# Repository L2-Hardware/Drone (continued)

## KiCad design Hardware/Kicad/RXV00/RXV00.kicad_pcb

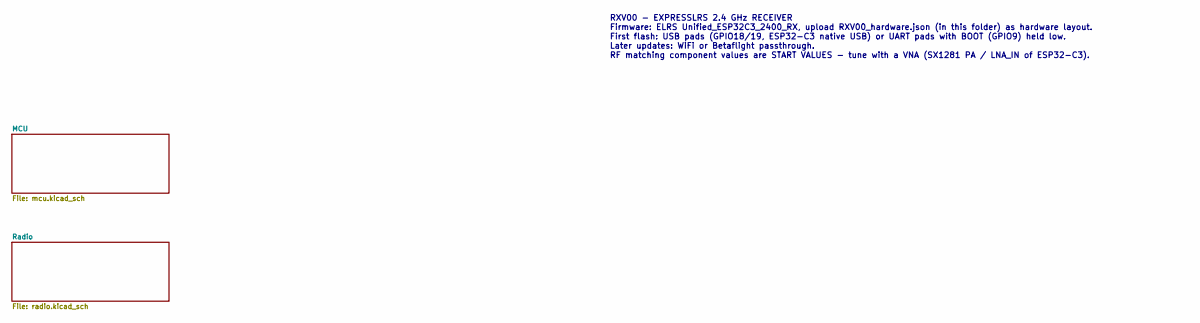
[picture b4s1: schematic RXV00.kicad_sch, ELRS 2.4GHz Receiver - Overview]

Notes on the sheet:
RXV00 - EXPRESSLRS 2.4 GHz RECEIVER Firmware: ELRS Unified_ESP32C3_2400_RX, upload RXV00_hardware.json (in this folder) as hardware layout. First flash: USB pads (GPIO18/19, ESP32-C3 native USB) or UART pads with BOOT (GPIO9) held low. Later updates: WiFi or Betaflight passthrough. RF matching comp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

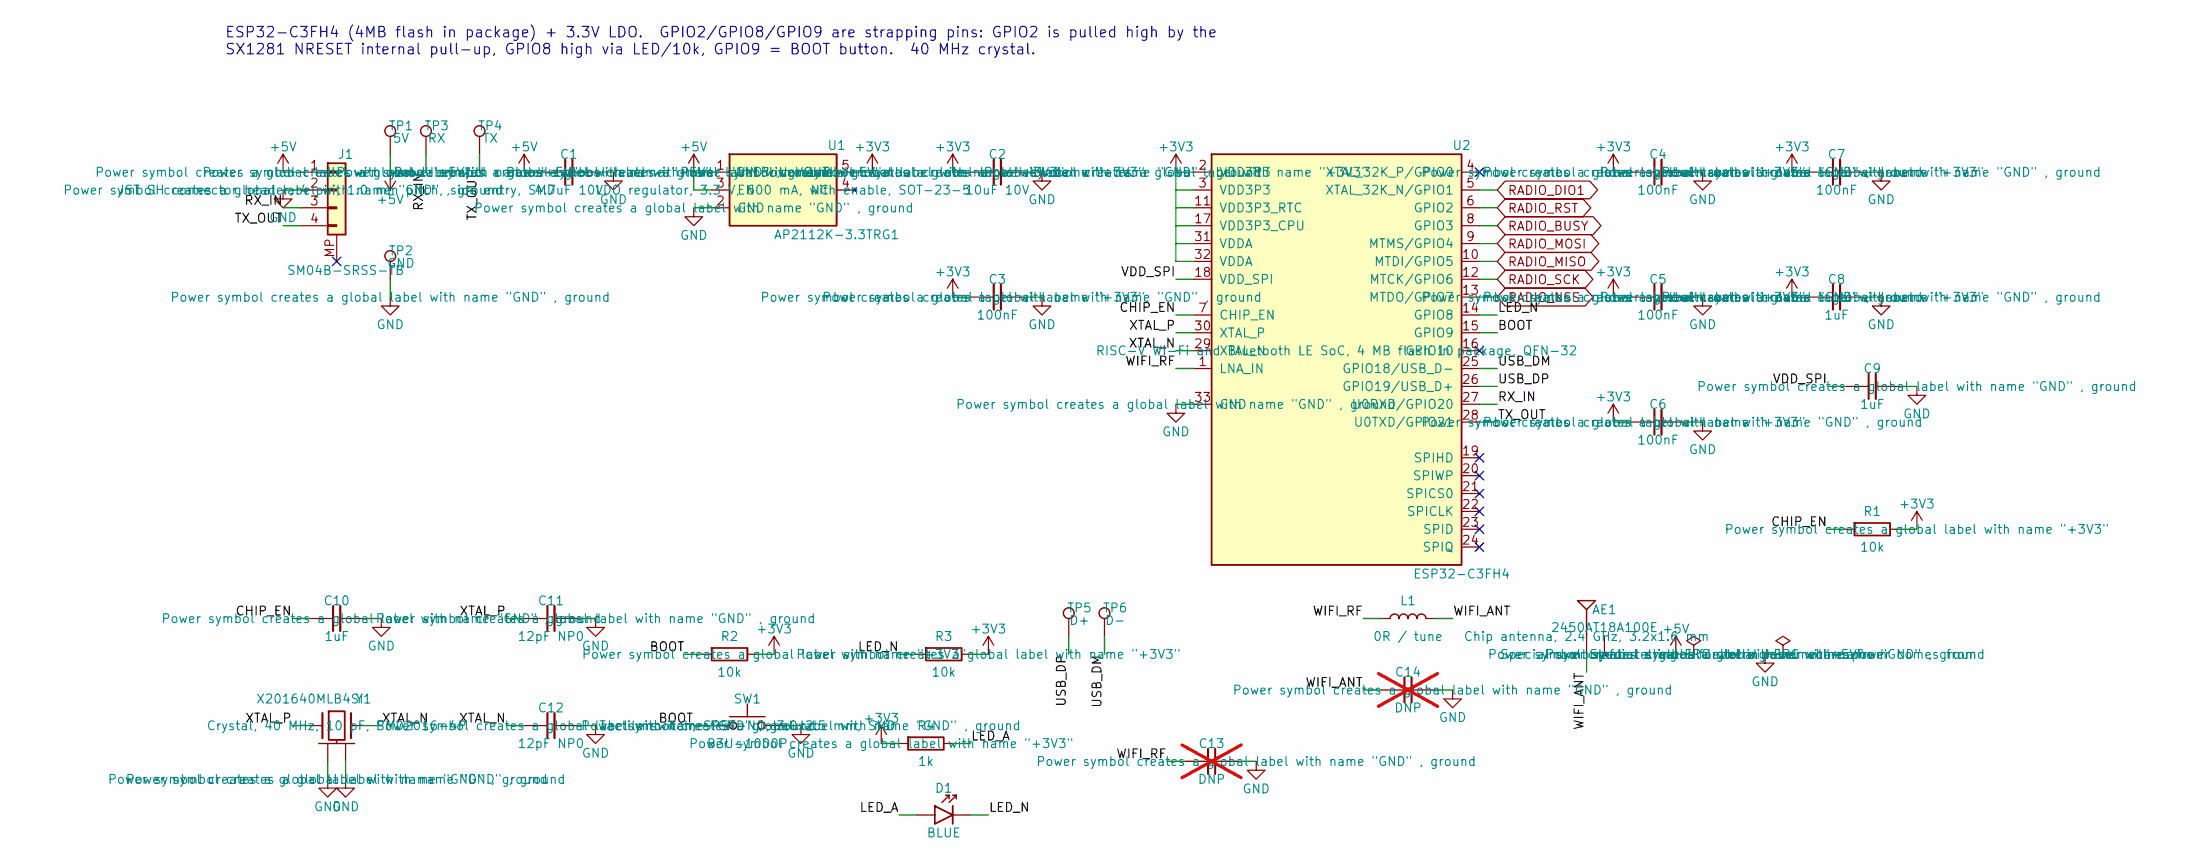
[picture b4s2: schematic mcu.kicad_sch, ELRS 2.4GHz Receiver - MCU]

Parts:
AE1: 2450AT18A100E
C1: 4.7uF 10V; C_0603_1608Metric
C2: 10uF 10V; C_0603_1608Metric
C3, C4, C5, C6, C7: 100nF; C_0402_1005Metric
C8, C9, C10: 1uF; C_0402_1005Metric
C11, C12: 12pF NP0; C_0402_1005Metric
C13, C14: DNP; C_0402_1005Metric; not fitted
D1: BLUE; LED_0603_1608Metric
J1: SM04B-SRSS-TB
L1: 0R / tune; L_0402_1005Metric
R1, R2, R3: 10k; R_0402_1005Metric
R4: 1k; R_0402_1005Metric
SW1: B3U-1000P
TP1: 5V; TestPoint_Pad_D1.5mm
TP2: GND; TestPoint_Pad_D1.5mm
TP3: RX; TestPoint_Pad_D1.5mm
TP4: TX; TestPoint_Pad_D1.5mm
TP5: D+; TestPoint_Pad_D1.0mm
TP6: D-; TestPoint_Pad_D1.0mm
U1: AP2112K-3.3TRG1
U2: ESP32-C3FH4
Y1: X201640MLB4SI

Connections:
+3V3: C2.1, C3.1, C4.1, C5.1, C6.1, C7.1, C8.1, R1.2, R2.2, R3.2, R4.1, U1.5 (VOUT), U2.2 (VDD3P3), U2.3 (VDD3P3), U2.11 (VDD3P3_RTC), U2.17 (VDD3P3_CPU), U2.31 (VDDA), U2.32 (VDDA); also elsewhere on the board
+5V: C1.1, J1.1, TP1.1, U1.1 (VIN), U1.3 (EN)
/MCU/BOOT: R2.1, SW1.1, U2.15 (GPIO9)
/MCU/CHIP_EN: C10.1, R1.1, U2.7 (CHIP_EN)
/MCU/LED_A: D1.2 (A), R4.2
/MCU/LED_N: D1.1 (K), R3.1, U2.14 (GPIO8)
/MCU/RX_IN: J1.3, TP3.1, U2.27 (U0RXD/GPIO20)
/MCU/TX_OUT: J1.4, TP4.1, U2.28 (U0TXD/GPIO21)
/MCU/USB_DM: TP6.1, U2.25 (GPIO18/USB_D-)
/MCU/USB_DP: TP5.1, U2.26 (GPIO19/USB_D+)
/MCU/VDD_SPI: C9.1, U2.18 (VDD_SPI)
/MCU/WIFI_ANT: AE1.1 (FEED), C14.1, L1.2
/MCU/WIFI_RF: C13.1, L1.1, U2.1 (LNA_IN)
/MCU/XTAL_N: C12.1, U2.29 (XTAL_N), Y1.3
/MCU/XTAL_P: C11.1, U2.30 (XTAL_P), Y1.1
GND: C1.2, C2.2, C3.2, C4.2, C5.2, C6.2, C7.2, C8.2, C9.2, C10.2, C11.2, C12.2, C13.2, C14.2, J1.2, SW1.2, TP2.1, U1.2 (GND), U2.33 (GND), Y1.2 (GND), Y1.4 (GND); also elsewhere on the board
RADIO_BUSY: U2.8 (GPIO3); also elsewhere on the board
RADIO_DIO1: U2.5 (XTAL_32K_N/GPIO1); also elsewhere on the board
RADIO_MISO: U2.10 (MTDI/GPIO5); also elsewhere on the board
RADIO_MOSI: U2.9 (MTMS/GPIO4); also elsewhere on the board
RADIO_NSS: U2.13 (MTDO/GPIO7); also elsewhere on the board
RADIO_RST: U2.6 (GPIO2); also elsewhere on the board
RADIO_SCK: U2.12 (MTCK/GPIO6); also elsewhere on the board

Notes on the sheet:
ESP32-C3FH4 (4MB flash in package) + 3.3V LDO. GPIO2/GPIO8/GPIO9 are strapping pins: GPIO2 is pulled high by the SX1281 NRESET internal pull-up, GPIO8 high via LED/10k, GPIO9 = BOOT button. 40 MHz crystal.

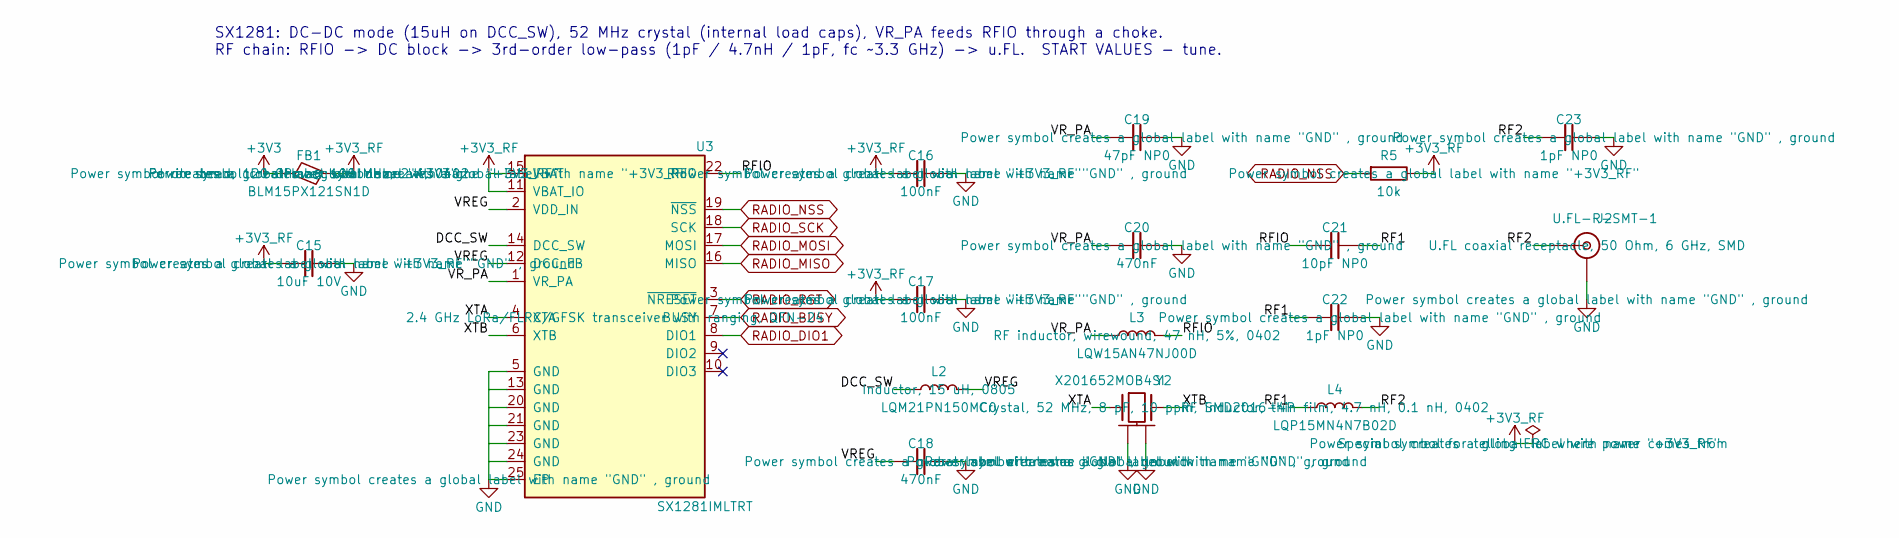
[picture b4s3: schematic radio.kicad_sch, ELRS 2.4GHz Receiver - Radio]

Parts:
C15: 10uF 10V; C_0603_1608Metric
C16, C17: 100nF; C_0402_1005Metric
C18, C20: 470nF; C_0402_1005Metric
C19: 47pF NP0; C_0402_1005Metric
C21: 10pF NP0; C_0402_1005Metric
C22, C23: 1pF NP0; C_0402_1005Metric
FB1: BLM15PX121SN1D
J2: U.FL-R-SMT-1
L2: LQM21PN150MC0
L3: LQW15AN47NJ00D
L4: LQP15MN4N7B02D
R5: 10k; R_0402_1005Metric
U3: SX1281IMLTRT
Y2: X201652MOB4SI

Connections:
+3V3: FB1.1; also elsewhere on the board
+3V3_RF: C15.1, C16.1, C17.1, FB1.2, R5.2, U3.11 (VBAT_IO), U3.15 (VBAT)
/Radio/DCC_SW: L2.1, U3.14 (DCC_SW)
/Radio/RF1: C21.2, C22.1, L4.1
/Radio/RF2: C23.1, J2.1 (In), L4.2
/Radio/RFIO: C21.1, L3.2, U3.22 (RFIO)
/Radio/VREG: C18.1, L2.2, U3.2 (VDD_IN), U3.12 (DCC_FB)
/Radio/VR_PA: C19.1, C20.1, L3.1, U3.1 (VR_PA)
/Radio/XTA: U3.4 (XTA), Y2.1
/Radio/XTB: U3.6 (XTB), Y2.3
GND: C15.2, C16.2, C17.2, C18.2, C19.2, C20.2, C22.2, C23.2, J2.2 (Ext), U3.5 (GND), U3.13 (GND), U3.20 (GND), U3.21 (GND), U3.23 (GND), U3.24 (GND), U3.25 (EP), Y2.2 (GND), Y2.4 (GND); also elsewhere on the board
RADIO_BUSY: U3.7 (BUSY); also elsewhere on the board
RADIO_DIO1: U3.8 (DIO1); also elsewhere on the board
RADIO_MISO: U3.16 (MISO); also elsewhere on the board
RADIO_MOSI: U3.17 (MOSI); also elsewhere on the board
RADIO_NSS: R5.1, U3.19 (~NSS); also elsewhere on the board
RADIO_RST: U3.3 (~NRESET); also elsewhere on the board
RADIO_SCK: U3.18 (SCK); also elsewhere on the board

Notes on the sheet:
SX1281: DC-DC mode (15uH on DCC_SW), 52 MHz crystal (internal load caps), VR_PA feeds RFIO through a choke. RF chain: RFIO -> DC block -> 3rd-order low-pass (1pF / 4.7nH / 1pF, fc ~3.3 GHz) -> u.FL. START VALUES - tune.

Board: 4 copper layers, 49 parts (0 on the bottom side), 32 nets, no tracks yet.

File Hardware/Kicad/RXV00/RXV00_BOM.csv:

"Qty","References","Value","Footprint","DNP"
"1","AE1","2450AT18A100E","eAntenna:2450AT18A100E",""
"1","C1","4.7uF 10V","eCapacitor:C_0603_1608Metric",""
"2","C2,C15","10uF 10V","eCapacitor:C_0603_1608Metric",""
"7","C3,C4,C5,C6,C7,C16,C17","100nF","eCapacitor:C_0402_1005Metric",""
"3","C8,C9,C10","1uF","eCapacitor:C_0402_1005Metric",""
"2","C11,C12","12pF NP0","eCapacitor:C_0402_1005Metric",""
"2","C13,C14","DNP","eCapacitor:C_0402_1005Metric","DNP"
"2","C18,C20","470nF","eCapacitor:C_0402_1005Metric",""
"1","C19","47pF NP0","eCapacitor:C_0402_1005Metric",""
"1","C21","10pF NP0","eCapacitor:C_0402_1005Metric",""
"2","C22,C23","1pF NP0","eCapacitor:C_0402_1005Metric",""
"1","D1","BLUE","eLED:LED_0603_1608Metric",""
"1","FB1","BLM15PX121SN1D","eFerrite:BLM15PX121SN1D",""
"1","J1","SM04B-SRSS-TB","eConnector:SM04B-SRSS-TB",""
"1","J2","U.FL-R-SMT-1","eConnector:U.FL-R-SMT-1",""
"1","L1","0R / tune","eCoil:L_0402_1005Metric",""
"1","L2","LQM21PN150MC0","eCoil:LQM21PN150MC0",""
"1","L3","LQW15AN47NJ00D","eCoil:LQW15AN47NJ00D",""
"1","L4","LQP15MN4N7B02D","eCoil:LQP15MN4N7B02D",""
"4","R1,R2,R3,R5","10k","eResistor:R_0402_1005Metric",""
"1","R4","1k","eResistor:R_0402_1005Metric",""
"1","SW1","B3U-1000P","eSwitch:B3U-1000P",""
"1","U1","AP2112K-3.3TRG1","eLinearReg:AP2112K-3.3TRG1",""
"1","U2","ESP32-C3FH4","eMCU:ESP32-C3FH4",""
"1","U3","SX1281IMLTRT","eRFModule:SX1281IMLTRT",""
"1","Y1","X201640MLB4SI","eCrystal:X201640MLB4SI",""
"1","Y2","X201652MOB4SI","eCrystal:X201652MOB4SI",""

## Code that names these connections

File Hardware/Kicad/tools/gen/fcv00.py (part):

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B.root_notes.append(
    "FCV00 - FLIGHT CONTROLLER\n"
    "MCU pin map (STM32F405RGT6)\n"
    "  SPI1 PA5/PA6/PA7  CS PA4  INT PC4  CLKIN PB0 -> ICM-42688-P (gyro)\n"
    "  SPI2 PB13/PB14/PB15  CS PB12        -> AT7456E (OSD)\n"
    "  SPI3 PB3/PB4/PB5  CS PA15           -> W25Q128 (blackbox)\n"
    "  I2C1 PB8/PB9                        -> LPS22DF baro + GPS compass\n"
    "  USART1 PB6/PB7 -> ELRS RX     USART2 PA2/PA3 -> VTX (MSP/SmartAudio)\n"
    "  USART3 PB10/PB11 -> GPS       UART4 PA0/PA1 -> AUX\n"
    "  UART5 PC12 (AUX TX) / PD2 (ESC telemetry RX)\n"
    "  MOTOR1..4 PC6..PC9 = TIM8 CH1..CH4 (DShot / bidir DShot)\n"
    "  LED strip PA8 (TIM1 CH1)   Buzzer PC5   LEDs PC14/PC15\n"
    "  ADC: VBAT PC2 (x11 divider), CURRENT PC1, USB VBUS detect PA9\n")

# ============================================================================ POWER
s = B.sheet("Power", "power.kicad_sch")
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for v, rtop, rbot, L, cout, rc, cc, chf in (("5V", "53.6k 1%", "10.2k 1%", "6.8uH SRP5030T-6R8M", "22uF 16V X5R", "16.9k", "6.8nF", "47pF"),
                                            ("10V", "115k 1%", "10k 1%", "10uH SRP5030T-100M", "22uF 25V X5R", "24.9k", "4.7nF", "33pF")):
    net = "+" + v
    s.add("eConverterDCDC:TPS54360BDDAR", pins={"VIN": "VBAT", "EN": "BUCK_EN", "RT/CLK": f"RT_{v}", "COMP": f"COMP_{v}",
                                                "GND": "GND", "GNDPAD": "GND", "BOOT": f"BOOT_{v}", "SW": f"SW_{v}", "FB": f"FB_{v}"})
    s.C("2.2uF 50V", "VBAT", fp=P.C0805)
    s.C("100nF 50V", "VBAT", fp=P.C0603)
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s = B.sheet("MCU", "mcu.kicad_sch")
s.note("MCU: STM32F405RGT6 168 MHz, HSE 8 MHz.  BOOT0 button = DFU over USB-C.  SWD on test pads.")
mcu = {
    "VBAT": "+3V3", "VDD": "+3V3", "VDDA": "VDDA", "NRST": "NRST", "BOOT0": "BOOT0", "PH0": "OSC_IN", "PH1": "OSC_OUT",
    "VCAP_1": "VCAP1", "VCAP_2": "VCAP2", "VSSA": "GND", "VSS": "GND",
    "PA0": "UART4_TX", "PA1": "UART4_RX", "PA2": "UART2_TX", "PA3": "UART2_RX", "PA4": "GYRO_CS", "PA5": "SPI1_SCK",
    "PA6": "SPI1_MISO", "PA7": "SPI1_MOSI", "PA8": "LED_STRIP", "PA9": "USB_VBUS_DET", "PA10": "NC", "PA11": "USB_DM",
    "PA12": "USB_DP", "PA13": "SWDIO", "PA14": "SWCLK", "PA15": "FLASH_CS",
    "PB0": "GYRO_CLKIN", "PB1": "PWM5", "PB2": "BOOT1", "PB3": "SPI3_SCK", "PB4": "SPI3_MISO", "PB5": "SPI3_MOSI",
    "PB6": "UART1_TX", "PB7": "UART1_RX", "PB8": "I2C1_SCL", "PB9": "I2C1_SDA", "PB10": "UART3_TX", "PB11": "UART3_RX",
    "PB12": "OSD_CS", "PB13": "SPI2_SCK", "PB14": "SPI2_MISO", "PB15": "SPI2_MOSI",
    "PC0": "NC", "PC1": "CURR_ADC", "PC2": "VBAT_ADC", "PC3": "NC", "PC4": "GYRO_INT1", "PC5": "BUZZER",
    "PC6": "MOTOR1", "PC7": "MOTOR2", "PC8": "MOTOR3", "PC9": "MOTOR4", "PC10": "NC", "PC11": "NC", "PC12": "UART5_TX",
    "PC13": "NC", "PC14": "LED0", "PC15": "LED1", "PD2": "UART5_RX"}
s.add("eMCU:STM32F405RGT6", pins=mcu)
for _ in range(5):
    s.C("100nF", "+3V3")
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    s.R("1k", "+3V3", f"{led}_A")
    s.LED(col, f"{led}_A", led)
# USB-C
s.add("eConnector:USB_C_GCT_USB4105-GF-A", pins={"VBUS": "VBUS", "CC1": "USB_CC1", "CC2": "USB_CC2", "D+": "USB_DP",
                                                  "D-": "USB_DM", "SBU1": "NC", "SBU2": "NC", "GND": "GND", "SHIELD": "GND"})
s.R("5.1k", "USB_CC1", "GND")
s.R("5.1k", "USB_CC2", "GND")
s.add("eDiodes:USBLC6-2SC6", pins={"I/O1": "USB_DP", "I/O2": "USB_DM", "VBUS": "VBUS", "GND": "GND"})
s.C("1uF 16V", "VBUS")
s.R("10k", "VBUS", "USB_VBUS_DET")
s.R("20k", "USB_VBUS_DET", "GND")

# ============================================================================ SENSORS
s = B.sheet("Sensors", "sensors.kicad_sch")
s.note("SENSORS: ICM-42688-P on dedicated SPI1 + own LDO (+3V3_GYRO). INT2/CLKIN driven by PB0 (TIM3) for external 32 kHz clock.\n"
       "LPS22DF baro on I2C1 (addr 0x5C, SA0=0). W25Q128JV blackbox flash on SPI3.")
s.add("eSensor:ICM-42688-P", pins={"VDD": "+3V3_GYRO", "VDDIO": "+3V3_GYRO", "AP_CS": "GYRO_CS", "AP_SCL/AP_SCLK": "SPI1_SCK",
                                    "AP_SDA/AP_SDIO/AP_SDI": "SPI1_MOSI", "AP_SDO/AP_AD0": "SPI1_MISO", "GND": "GND",
                                    "INT1/INT": "GYRO_INT1", "INT2/FSYNC/CLKIN": "GYRO_CLKIN"})
s.C("100nF", "+3V3_GYRO")
s.C("1uF", "+3V3_GYRO")
s.C("100nF", "+3V3_GYRO")
s.R("10k", "GYRO_CS", "+3V3_GYRO")
s.add("eSensor:LPS22DF", pins={"VDD": "+3V3", "Vdd_IO": "+3V3", "SCL": "I2C1_SCL", "SDA": "I2C1_SDA", "SA0": "GND",
                                "~{CS}": "+3V3", "INT_DRDY": "NC", "GND_IO": "GND", "GND": "GND"})
s.C("100nF", "+3V3")
s.R("2.2k", "I2C1_SCL", "+3V3")
s.R("2.2k", "I2C1_SDA", "+3V3")
s.add("eMemory:W25Q128JVSIQ", pins={"VCC": "+3V3", "~{CS}": "FLASH_CS", "CLK": "SPI3_SCK", "DI(IO0)": "SPI3_MOSI",
                                     "DO(IO1)": "SPI3_MISO", "IO2": "FLASH_WP", "IO3": "FLASH_HOLD", "GND": "GND"})
s.C("100nF", "+3V3")
s.R("10k", "FLASH_CS", "+3V3")
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       "J ESC 8p: VBAT GND CURR TLM M1 M2 M3 M4 (matches ESCV00)   J RX 4p: 5V GND TX RX (matches RXV00)\n"
       "J VTX 6p: 10V 5V GND VIDEO TX RX (matches VTXV00)   J CAM 3p: PWR GND VIDEO (PWR = 5V or 10V by solder jumper)\n"
       "J GPS 6p: 5V GND TX RX SCL SDA     J AUX 6p: 5V GND UART4_TX UART4_RX UART5_TX PWM5")
s.add("eConnector:JST_SH_SM08B-SRSS-TB", "ESC", pins={"1": "VBAT", "2": "GND", "3": "ESC_CURR", "4": "UART5_RX", "5": "MOTOR1",
                                                       "6": "MOTOR2", "7": "MOTOR3", "8": "MOTOR4", "MP": "NC"})
s.R("1k", "ESC_CURR", "CURR_ADC")
s.C("100nF", "CURR_ADC")
s.add("eConnector:JST_SH_SM04B-SRSS-TB", "RX", pins={"1": "+5V", "2": "GND", "3": "UART1_TX", "4": "UART1_RX", "MP": "NC"})
s.add("eConnector:JST_SH_SM06B-SRSS-TB", "VTX", pins={"1": "+10V", "2": "+5V", "3": "GND", "4": "VID_OUT", "5": "UART2_TX",
                                                       "6": "UART2_RX", "MP": "NC"})
s.add("eConnector:JST_SH_SM03B-SRSS-TB", "CAM", pins={"1": "CAM_PWR", "2": "GND", "3": "CAM_VIDEO", "MP": "NC"})
s.add("eJumpers:SolderJumper_3", "CAM 5V|10V", pins={"1": "+5V", "2": "CAM_PWR", "3": "+10V"})
s.C("10uF 25V", "CAM_PWR", fp=P.C0805)
s.add("eConnector:JST_SH_SM06B-SRSS-TB", "GPS", pins={"1": "+5V", "2": "GND", "3": "UART3_TX", "4": "UART3_RX", "5": "I2C1_SCL",
                                                       "6": "I2C1_SDA", "MP": "NC"})
s.add("eConnector:JST_SH_SM06B-SRSS-TB", "AUX", pins={"1": "+5V", "2": "GND", "3": "UART4_TX", "4": "UART4_RX", "5": "UART5_TX",
                                                       "6": "PWM5", "MP": "NC"})
# LED strip + buzzer pads
s.R("33R", "LED_STRIP", "LED_DOUT")
s.TP("LED_DOUT", P.TP20, "LED")
s.TP("+5V", P.TP20, "5V")
s.TP("GND", P.TP20, "GND")
s.add("eTransistor:2N7002", pins={"G": "BUZZER_G", "S": "GND", "D": "BUZZER_N"})
s.R("1k", "BUZZER", "BUZZER_G")
s.R("100k", "BUZZER_G", "GND")
s.D("D", "1N4148W", "BUZZER_N", "+5V", P.D_SOD123, fields={"MPN": "1N4148W"})
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
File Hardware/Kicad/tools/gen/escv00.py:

"""ESCV00 - 4-in-1 ESC for AM32 firmware.

Per channel: STM32F051K8U6 (or pin-compatible AT32F421K8U7) + DRV8300D 3-phase gate driver + 6x BSZ018N04LS6.
Pin-out follows AM32 HARDWARE_GROUP_F0_B / HARDWARE_GROUP_AT_B + AT_045 (same pins on both MCUs):
  input PB4 (TIM3_CH1), phase A: PA10 high / PB1 low, B: PA9 / PB0, C: PA8 / PA7,
  comparator: PA0 = phase A, PA4 = phase B, PA5 = phase C, PA1 = virtual neutral (COMP1 INP),
  VBAT ADC PA6 (10k/1k divider, AM32 default VOLTAGE_DIVIDER 110), telemetry TX PB6 (USART1).
"""
import parts as P
import project
from schgen import Board

B = Board("ESCV00", "4-in-1 ESC", "V00",
          comments=["4x (STM32F051K8U6 / AT32F421K8U7 + DRV8300D + 6x BSZ018N04LS6), AM32 firmware",
                    "2S-6S, 30.5x30.5 mm pattern, 6-layer 2oz recommended",
                    "Total current shunt 0.25 mOhm + INA181A3 -> 25 mV/A to FC"])
B.root_notes.append(
    "ESCV00 - 4-IN-1 ESC (AM32)\n"
    "Channel sheet is used 4 times (CH1..CH4 -> MOTOR1..4, M1_x..M4_x).\n"
    "Flash the AM32 bootloader once per MCU via the SWD pads (SWDIO/SWCLK/NRST + 3V3/GND),\n"
    "then update firmware over the signal wire (Betaflight passthrough / AM32 configurator).\n"
    "AM32 target: F051 -> HARDWARE_GROUP_F0_B, AT32F421 -> HARDWARE_GROUP_AT_B + HARDWARE_GROUP_AT_045\n"
    "  (identical to the TBS_6S_4IN1_F421 pin-out). Set DEAD_TIME to suit the DRV8300 + BSZ018N04LS6.\n"
    "Current: 4x 1 mOhm 2512 in parallel (0.25 mOhm) x INA181A3 (100 V/V) = 25 mV/A  -> Betaflight ibata_scale 250\n"
    "Battery voltage to FC: VBAT on connector pin 1 (FC measures it itself).\n")

# ============================================================================ CHANNEL (x4)
ch = B.sheet("Channel", "channel.kicad_sch",
             instances=[{"name": f"CH{i}", "ref_base": i * 100,
                         "portmap": {"SIG_IN": f"MOTOR{i}", "TLM": "ESC_TLM", "PH_A": f"M{i}_A", "PH_B": f"M{i}_B",
                                     "PH_C": f"M{i}_C"}} for i in (1, 2, 3, 4)],
             ports=["SIG_IN", "TLM", "PH_A", "PH_B", "PH_C"], globals_=["ESC_VBAT_SENSE"])
ch.note("ESC CHANNEL: MCU (AM32) -> DRV8300D (bootstrap diodes integrated, MODE/DT open = non-inverted, fixed dead time)\n"
        "Back-EMF sense: phase dividers 20k/2.2k to PA0/PA4/PA5, virtual neutral 3x 20k + 750R to PA1.  Gate R 4.7R.")
ch.add("eMCU:STM32F051K8U6", pins={
    "VDD": "+3V3", "VDDA": "VDDA", "NRST": "NRST", "BOOT0": "BOOT0", "PF0": "NC", "PF1": "NC", "VSS": "GND",
    "PA0": "SENSE_A", "PA1": "SENSE_N", "PA2": "NC", "PA3": "NC", "PA4": "SENSE_B", "PA5": "SENSE_C",
    "PA6": "ESC_VBAT_SENSE", "PA7": "C_LO", "PA8": "C_HI", "PA9": "B_HI", "PA10": "A_HI", "PA11": "NC", "PA12": "NC",
    "PA13": "SWDIO", "PA14": "SWCLK", "PA15": "NC", "PB0": "B_LO", "PB1": "A_LO", "PB2": "NC", "PB3": "NC",
    "PB4": "SIG_MCU", "PB5": "NC", "PB6": "TLM_MCU", "PB7": "NC", "PB8": "NC"})
ch.C("100nF", "+3V3")
ch.C("100nF", "+3V3")
ch.C("1uF", "+3V3")
ch.FB("120R@100MHz", "+3V3", "VDDA", fp=P.FB0402, fields={"MPN": "BLM15PX121SN1D"})
ch.C("1uF", "VDDA")
ch.C("100nF", "VDDA")
ch.R("10k", "BOOT0", "GND")
ch.C("100nF", "NRST")
ch.R("100R", "SIG_IN", "SIG_MCU")
ch.R("1k", "TLM_MCU", "TLM")
for n in ("SWDIO", "SWCLK", "NRST"):
    ch.TP(n, P.TP10)
ch.add("eInterface:DRV8300DRGER", pins={
    "GVDD": "+10V", "GND": "GND", "EP": "GND", "MODE": "NC", "DT": "NC",
    "INHA": "A_HI", "INLA": "A_LO", "INHB": "B_HI", "INLB": "B_LO", "INHC": "C_HI", "INLC": "C_LO",
    "BSTA": "BST_A", "GHA": "GHA_DRV", "SHA": "PH_A", "GLA": "GLA_DRV",
    "BSTB": "BST_B", "GHB": "GHB_DRV", "SHB": "PH_B", "GLB": "GLB_DRV",
    "BSTC": "BST_C", "GHC": "GHC_DRV", "SHC": "PH_C", "GLC": "GLC_DRV"})
ch.C("10uF 25V", "+10V", fp=P.C0805)
ch.C("100nF", "+10V")
for ph in "ABC":
    ch.C("1uF 25V X7R", f"BST_{ph}", f"PH_{ph}", fp=P.C0603)
    ch.R("4.7R", f"GH{ph}_DRV", f"GH_{ph}")
    ch.R("4.7R", f"GL{ph}_DRV", f"GL_{ph}")
    ch.add("eTransistor:BSZ018N04LS6", pins={"G": f"GH_{ph}", "D": "VBAT", "S": f"PH_{ph}"})
    ch.add("eTransistor:BSZ018N04LS6", pins={"G": f"GL_{ph}", "D": f"PH_{ph}", "S": "GND"})
    ch.R("20k", f"PH_{ph}", f"SENSE_{ph}")
    ch.R("2.2k", f"SENSE_{ph}", "GND")
    ch.R("20k", f"PH_{ph}", "SENSE_N")
ch.R("750R", "SENSE_N", "GND")
ch.C("10uF 50V X7R", "VBAT", fp=P.C1206)
ch.C("10uF 50V X7R", "VBAT", fp=P.C1206)
ch.C("100nF 50V", "VBAT", fp=P.C0603)

# ============================================================================ POWER / IO
s = B.sheet("Power", "power.kicad_sch")
s.note("POWER: battery pads, current shunt (low side), 10V gate-driver rail (LMR16006Y, 2.1 MHz), 3.3V LDO for the 4 MCUs.\n"
       "Add a 470-1000uF 35V low-ESR electrolytic on the battery leads (not on the PCB).\n"
       "LMR16006: Vout = 0.765V x (1 + 121k/10k) = 10.0V.  Shunt: BAT- pad -> 4x 1mOhm -> board GND.")
s.TP("VBAT", P.PAD5x8, "BAT+")
s.TP("BAT_N", P.PAD5x8, "BAT-")
for _ in range(4):
    s.R("1mR 3W", "GND", "BAT_N", fp=P.R2512, fields={"MPN": "WSLP2512R0010FEA", "Manufacturer": "Vishay"})
s.R("10R", "GND", "ISNS_P")
s.R("10R", "BAT_N", "ISNS_N")
s.C("100nF", "ISNS_P", "ISNS_N")
s.add("eAmplifier:INA181A3IDBVR", pins={"V+": "+3V3", "GND": "GND", "+": "ISNS_P", "-": "ISNS_N", "REF": "GND", "~": "CURR_OUT"})
s.C("100nF", "+3V3")
s.R("1k", "CURR_OUT", "ESC_CURR")
s.C("10nF", "ESC_CURR")
# shared battery sense for the 4 MCUs (AM32 low-voltage cut-off / telemetry)
s.R("10k 1%", "VBAT", "ESC_VBAT_SENSE")
s.R("1k 1%", "ESC_VBAT_SENSE", "GND")
s.C("100nF", "ESC_VBAT_SENSE")
# 10 V gate driver rail
s.add("eConverterDCDC:LMR16006YDDCR", pins={"VIN": "VBAT", "~{SHDN}": "EN_10V", "GND": "GND", "CB": "CB_10V",
                                             "SW": "SW_10V", "FB": "FB_10V"})
s.R("100k", "VBAT", "EN_10V")
s.C("2.2uF 50V", "VBAT", fp=P.C0805)
s.C("100nF 50V", "VBAT", fp=P.C0603)
s.C("100nF", "CB_10V", "SW_10V")
s.D("D_Schottky", "PMEG6010CEH", "GND", "SW_10V", P.D_SOD123F, fields={"MPN": "PMEG6010CEH,115"})
s.L("10uH SWPA3012S-100MT", "SW_10V", "+10V", fp=P.L_SWPA3012, fields={"MPN": "SWPA3012S100MT", "Manufacturer": "Sunlord"})
s.R("121k 1%", "+10V", "FB_10V")
s.R("10k 1%", "FB_10V", "GND")
s.C("10uF 25V", "+10V", fp=P.C0805)
s.C("10uF 25V", "+10V", fp=P.C0805)
# 3.3 V
s.add("eLinearReg:MCP1703AT-3302E_MB", pins={"VI": "+10V", "GND": "GND", "VO": "+3V3"})
s.C("1uF 25V", "+10V", fp=P.C0603)
s.C("4.7uF 10V", "+3V3", fp=P.C0603)
s.R("1k", "+3V3", "LED_PWR_A")
s.LED("GREEN", "LED_PWR_A", "GND")
for n in ("+3V3", "GND", "+10V"):
    s.TP(n, P.TP15)
# FC connector
s.add("eConnector:JST_SH_SM08B-SRSS-TB", "FC", pins={"1": "VBAT", "2": "GND", "3": "ESC_CURR", "4": "ESC_TLM", "5": "MOTOR1",
                                                      "6": "MOTOR2", "7": "MOTOR3", "8": "MOTOR4", "MP": "NC"})
s.R("10k", "ESC_TLM", "+3V3")
# motor pads
for m in (1, 2, 3, 4):
    for ph in "ABC":
        s.TP(f"M{m}_{ph}", P.PAD3x5, f"M{m}{ph}")
for _ in range(4):
    s.add("eMechanical:MountingHole", "M3", P.MH_M3, {})

NETCLASSES = (
    [project.netclass("Default", 0.15), project.netclass("Power", 1.0, clearance=0.2, via_d=0.6, via_drill=0.3),
     project.netclass("Gate", 0.25), project.netclass("Rail", 0.4)],
    [("VBAT", "Power"), ("GND", "Power"), ("BAT_N", "Power"), ("M?_?", "Power"), ("/CH?/GH_?", "Gate"),
     ("/CH?/GL_?", "Gate"), ("+10V", "Rail"), ("+3V3", "Rail")],
)

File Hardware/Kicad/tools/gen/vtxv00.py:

"""VTXV00 - analog 5.8 GHz video transmitter: RTC6705 + RFPA5542 + STM32F031G6U6 / GD32F130G6U6.

MCU pin-out follows OpenVTx target "Generic_GD32F130" (EWRF E7082VM clone):
  UART PA9 (single-wire SmartAudio/Tramp/MSP), RTC6705 bit-banged SPI: SS PB3, CLK PA15, MOSI PB4,
  LEDs PA4 red / PA3 green / PA2 blue, PA_EN ("VREF") PA0, PDET ("VPD") PA1, RTC_BIAS PWM PB5, button PA6.
"""
import parts as P
import project
from schgen import Board

B = Board("VTXV00", "5.8GHz Video Transmitter", "V00",
          comments=["RTC6705 FM video modulator + Qorvo RFPA5542 PA (up to ~400 mW), OpenVTx-compatible MCU",
                    "Connector matches FCV00 'VTX' port (10V 5V GND VIDEO TX RX)",
                    "4-layer, 50 ohm coplanar RF trace, heatsink/thermal vias under the PA"])
B.root_notes.append(
    "VTXV00 - 5.8 GHz ANALOG VTX\n"
    "Firmware: OpenVTx (target Generic_GD32F130 when populated with GD32F130G6U6) or custom firmware on STM32F031G6U6.\n"
    "Power control loop (from OpenVTx): PB5 PWM -> RC -> emitter follower -> RTC6705 BUFVDD, closed loop on RFPA5542 PDET.\n"
    "RF values (RTC6705 output match, attenuator pad, loop filters, harmonic filter) are START VALUES - tune on the bench.\n"
    "Legal: 25 mW EIRP licence-free in the EU (5.8 GHz SRD); higher power needs an amateur radio licence.\n")

# ============================================================================ CONTROL
s = B.sheet("Control", "control.kicad_sch")
s.note("CONTROL: 5V in -> RFPA5542 (via 3A ferrite), 3.3V LDO for MCU + RTC6705.\n"
       "MCU = STM32F031G6U6 footprint/pin-out (GD32F130G6U6 drop-in for OpenVTx).  SWD pads for first flashing.")
s.add("eConnector:JST_SH_SM06B-SRSS-TB", "FC", pins={"1": "NC", "2": "+5V", "3": "GND", "4": "VIDEO_IN", "5": "FC_TX",
                                                      "6": "FC_RX", "MP": "NC"})
s.C("22uF 10V", "+5V", fp=P.C0805)
s.C("100nF", "+5V")
s.FB("120R 3A", "+5V", "+5V_PA", fp=P.FB0603, fields={"MPN": "BLM18KG121TN1D", "Manufacturer": "Murata"})
s.C("22uF 10V", "+5V_PA", fp=P.C0805)
s.add("eLinearReg:AP2112K-3.3TRG1", pins={"VIN": "+5V", "EN": "+5V", "GND": "GND", "VOUT": "+3V3"})
s.C("1uF 16V", "+5V")
s.C("4.7uF 10V", "+3V3", fp=P.C0603)
s.add("eMCU:STM32F031G6U6", pins={
    "VDD": "+3V3", "VDDA": "+3V3", "VSS": "GND", "BOOT0": "BOOT0", "NRST": "NRST", "PF0": "NC", "PF1": "NC",
    "PA0": "PA_EN", "PA1": "VPD", "PA2": "LED_B", "PA3": "LED_G", "PA4": "LED_R", "PA5": "NC", "PA6": "BUTTON",
    "PA7": "NC", "PA8": "NC", "PA9": "UART_SA", "PA10": "UART_RX", "PA13": "SWDIO", "PA14": "SWCLK",
    "PA15": "RTC_CLK", "PB0": "NC", "PB1": "NC", "PB3": "RTC_LE", "PB4": "RTC_DATA", "PB5": "RTC_BIAS_PWM",
    "PB6": "NC", "PB7": "NC"})
s.C("100nF", "+3V3")
s.C("100nF", "+3V3")
s.C("1uF", "+3V3")
s.R("10k", "BOOT0", "GND")
s.C("100nF", "NRST")
s.R("100R", "FC_TX", "UART_SA")
s.R("100R", "FC_RX", "UART_RX")
for col, net in (("RED", "LED_R"), ("GREEN", "LED_G"), ("BLUE", "LED_B")):
    s.R("1k", net, f"{net}_A")
    s.LED(col, f"{net}_A", "GND")
s.R("10k", "BUTTON", "+3V3")
s.add("eSwitch:SW_Push", "BAND/CH", pins={"1": "BUTTON", "2": "GND"}, fields={"MPN": "B3U-1000P", "Manufacturer": "Omron"})
for n in ("SWDIO", "SWCLK", "NRST", "+3V3", "GND"):
    s.TP(n, P.TP10)
# output power control (OpenVTx RTC_BIAS)
s.R("10k", "RTC_BIAS_PWM", "BIAS_RC")
s.C("1uF", "BIAS_RC")
s.add("eTransistor:MMBT3904", pins={"B": "BIAS_RC", "C": "+3V3_RF", "E": "RTC_BUFVDD"})
s.C("100nF", "RTC_BUFVDD")

# ============================================================================ RF
s = B.sheet("RF", "rf.kicad_sch")
s.note("RF: RTC6705 (SPI mode, SPI_SE high, 8 MHz crystal) PAOUT1 (+2 dBm) -> 10 dB pi pad -> RFPA5542 (33 dB gain, ~25 dBm out) -> LPF -> u.FL\n"
       "RFPA5542: VCC 5V, R(VCC2) 0R (15R for better VSWR ruggedness), PA_EN 1nF, PDET 10pF -> MCU ADC (VPD).\n"
       "Video is DC-coupled into VT_MOD (75R input); C footprint available for AC coupling.  Audio PLLs unused.")
s.FB("120R@100MHz", "+3V3", "+3V3_RF", fp=P.FB0603, fields={"MPN": "BLM18PG121SN1D"})
s.C("10uF 10V", "+3V3_RF", fp=P.C0603)
s.add("eRFModule:RTC6705", pins={
    "VDD33_DIG": "+3V3_RF", "V2D5_PLL": "+3V3_RF", "AVDD_6": "+3V3_RF", "AVDD_6.5": "+3V3_RF", "VDD3V3": "+3V3_RF",
    "VDDVT": "+3V3_RF", "PAVDD": "+3V3_RF", "VCOVDD": "+3V3_RF", "LDD2V5": "+3V3_RF", "BUFVDD": "RTC_BUFVDD",
    "GND": "GND", "RFGND": "GND", "EP": "GND",
    "SPI_SE": "+3V3_RF", "S": "NC", "BX": "NC", "SPIDATA/CS0": "RTC_DATA", "SPILE/CS1": "RTC_LE", "SPICLK/CS2": "RTC_CLK",
    "VT_MOD": "VT_MOD", "RF_VT2": "RF_VT2", "AVT1": "AVT1", "ACP1": "ACP1", "AOUT1": "NC", "AVT2": "AVT2", "ACP2": "ACP2",
    "AOUT2": "NC", "REG1D8": "REG1D8", "REG1D8_1": "REG1D8_1", "XTAL1": "RTC_X1", "XTAL2": "RTC_X2",
    "CP": "RTC_CP", "VT": "RTC_VT", "PAOUT1": "RTC_RFOUT", "PAOUT2": "RTC_PAOUT2"})
for _ in range(6):
    s.C("100nF", "+3V3_RF")
s.C("1nF", "+3V3_RF")
s.C("1nF", "+3V3_RF")
s.C("1uF", "REG1D8")
s.C("1uF", "REG1D8_1")
s.add("eCrystal:Crystal_GND24", "8MHz 12pF", P.XTAL3225, {"1": "RTC_X1", "3": "RTC_X2", "2": "GND", "4": "GND"},
      fields={"MPN": "X322508MLB4SI", "Manufacturer": "Yangxing"})
s.C("18pF NP0", "RTC_X1")
s.C("18pF NP0", "RTC_X2")
# synthesizer loop filter (start values)
s.C("1nF", "RTC_CP")
s.R("4.7k", "RTC_CP", "LF_RC")
s.C("10nF", "LF_RC")
s.R("1k", "RTC_CP", "RTC_VT")
s.C("470pF", "RTC_VT")
# audio PLL loop filters (audio unused)
s.R("10k", "ACP1", "AVT1")
s.C("10nF", "AVT1")
s.R("10k", "ACP2", "AVT2")
s.C("10nF", "AVT2")
s.C("100nF", "RF_VT2")
# video input
s.R("0R", "VIDEO_IN", "VT_MOD")
s.R("75R", "VIDEO_IN", "GND", dnp=True)
s.C("10uF (AC option)", "VIDEO_IN", "VT_MOD", fp=P.C0603, dnp=True)
# RTC6705 output -> pi attenuator -> PA
s.R("0R (high pwr)", "RTC_PAOUT2", "RTC_RFOUT", dnp=True)
s.L("DNP (feed opt.)", "RTC_RFOUT", "+3V3_RF", fp=P.L0402, dnp=True)
s.C("10pF NP0", "RTC_RFOUT", "ATT_IN", fp=P.C0402)
s.R("97.6R", "ATT_IN", "GND")
s.R("71.5R", "ATT_IN", "ATT_OUT")
s.R("97.6R", "ATT_OUT", "GND")
s.C("10pF NP0", "ATT_OUT", "PA_IN", fp=P.C0402)
s.add("eAmplifier:RFPA5542", pins={"VCC1": "+5V_PA", "VCC2": "PA_VCC2", "VCC3": "+5V_PA", "GND": "GND", "EP": "GND",
                                    "RFIN": "PA_IN", "PA_EN": "PA_EN", "RFOUT": "PA_OUT", "PDET": "VPD"})
s.C("2.2uF", "+5V_PA", fp=P.C0402)
s.C("2.2uF", "+5V_PA", fp=P.C0402)
s.R("0R", "+5V_PA", "PA_VCC2", fp=P.R0402)
s.C("2.2uF", "PA_VCC2", fp=P.C0402)
s.C("1nF", "PA_EN")
s.C("10pF NP0", "VPD")
s.C("10pF NP0", "PA_OUT", "RF_F1", fp=P.C0402)
s.C("DNP", "RF_F1", fp=P.C0402, dnp=True)
s.L("0R / tune", "RF_F1", "RF_ANT", fp=P.L0402)
s.C("DNP", "RF_ANT", fp=P.C0402, dnp=True)
s.add("eConnector:Conn_Coaxial", "U.FL", P.UFL, {"1": "RF_ANT", "2": "GND"}, fields={"MPN": "U.FL-R-SMT-1(10)", "Manufacturer": "Hirose"})

NETCLASSES = ([project.netclass("Default", 0.15), project.netclass("RF_50R", 0.3, clearance=0.2),
               project.netclass("PA_Power", 0.6)],
              [("/RF/RF_*", "RF_50R"), ("/RF/PA_IN", "RF_50R"), ("/RF/PA_OUT", "RF_50R"), ("/RF/ATT_*", "RF_50R"),
               ("/RF/RTC_RFOUT", "RF_50R"), ("+5V_PA", "PA_Power"), ("+5V", "PA_Power")])

# 20x20 mm M2 mounting pattern (placed by pcbgen)
for _ in range(4):
    B.sheets[0].add("eMechanical:MountingHole", "M2", P.MH_M2, {})

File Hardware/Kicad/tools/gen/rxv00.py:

"""RXV00 - ExpressLRS 2.4 GHz receiver: ESP32-C3FH4 + SX1281.

GPIO map = ELRS "Generic C3 2400" layout (ExpressLRS/targets RX/Generic C3 2400.json):
  radio_busy 3, radio_dio1 1, radio_miso 5, radio_mosi 4, radio_nss 7, radio_rst 2, radio_sck 6,
  serial_rx 20, serial_tx 21, button 9.  LED: plain LED on GPIO8 (active low) -> see RXV00_hardware.json
"""
import json
import os

import parts as P
import project
from schgen import Board

B = Board("RXV00", "ELRS 2.4GHz Receiver", "V00",
          comments=["ESP32-C3FH4 + SX1281, ExpressLRS 3.5+ (Unified_ESP32C3_2400_RX)",
                    "Connector matches FCV00 'RX' port (5V GND TX RX), u.FL antenna",
                    "2-layer or 4-layer 0.8mm, controlled 50 ohm RF trace"])
B.root_notes.append(
    "RXV00 - EXPRESSLRS 2.4 GHz RECEIVER\n"
    "Firmware: ELRS Unified_ESP32C3_2400_RX, upload RXV00_hardware.json (in this folder) as hardware layout.\n"
    "First flash: USB pads (GPIO18/19, ESP32-C3 native USB) or UART pads with BOOT (GPIO9) held low.\n"
    "Later updates: WiFi or Betaflight passthrough.\n"
    "RF matching component values are START VALUES - tune with a VNA (SX1281 PA / LNA_IN of ESP32-C3).\n")

# ============================================================================ MCU + POWER
s = B.sheet("MCU", "mcu.kicad_sch")
s.note("ESP32-C3FH4 (4MB flash in package) + 3.3V LDO.  GPIO2/GPIO8/GPIO9 are strapping pins: GPIO2 is pulled high by the\n"
       "SX1281 NRESET internal pull-up, GPIO8 high via LED/10k, GPIO9 = BOOT button.  40 MHz crystal.")
s.add("eConnector:JST_SH_SM04B-SRSS-TB", "FC", pins={"1": "+5V", "2": "GND", "3": "RX_IN", "4": "TX_OUT", "MP": "NC"})
for n, lbl in (("+5V", "5V"), ("GND", "GND"), ("RX_IN", "RX"), ("TX_OUT", "TX")):
    s.TP(n, P.TP15, lbl)
s.C("4.7uF 10V", "+5V", fp=P.C0603)
s.add("eLinearReg:AP2112K-3.3TRG1", pins={"VIN": "+5V", "EN": "+5V", "GND": "GND", "VOUT": "+3V3"})
s.C("10uF 10V", "+3V3", fp=P.C0603)
s.C("100nF", "+3V3")
s.add("eMCU:ESP32-C3FH4", pins={
    "VDD3P3": "+3V3", "VDD3P3_RTC": "+3V3", "VDD3P3_CPU": "+3V3", "VDDA": "+3V3", "VDD_SPI": "VDD_SPI",
    "CHIP_EN": "CHIP_EN", "XTAL_P": "XTAL_P", "XTAL_N": "XTAL_N", "LNA_IN": "WIFI_RF", "GND": "GND",
    "XTAL_32K_P/GPIO0": "NC", "XTAL_32K_N/GPIO1": "RADIO_DIO1", "GPIO2": "RADIO_RST", "GPIO3": "RADIO_BUSY",
    "MTMS/GPIO4": "RADIO_MOSI", "MTDI/GPIO5": "RADIO_MISO", "MTCK/GPIO6": "RADIO_SCK", "MTDO/GPIO7": "RADIO_NSS",
    "GPIO8": "LED_N", "GPIO9": "BOOT", "GPIO10": "NC", "GPIO18/USB_D-": "USB_DM", "GPIO19/USB_D+": "USB_DP",
    "U0RXD/GPIO20": "RX_IN", "U0TXD/GPIO21": "TX_OUT",
    "SPIHD": "NC", "SPIWP": "NC", "SPICS0": "NC", "SPICLK": "NC", "SPID": "NC", "SPIQ": "NC"})
for _ in range(4):
    s.C("100nF", "+3V3")
s.C("1uF", "+3V3")
s.C("1uF", "VDD_SPI")
s.R("10k", "CHIP_EN", "+3V3")
s.C("1uF", "CHIP_EN")
s.add("eCrystal:Crystal_GND24", "40MHz 10pF", P.XTAL2016, {"1": "XTAL_P", "3": "XTAL_N", "2": "GND", "4": "GND"},
      fields={"MPN": "X201640MLB4SI", "Manufacturer": "Yangxing"})
s.C("12pF NP0", "XTAL_P")
s.C("12pF NP0", "XTAL_N")
s.R("10k", "BOOT", "+3V3")
s.add("eSwitch:SW_Push", "BOOT", pins={"1": "BOOT", "2": "GND"}, fields={"MPN": "B3U-1000P", "Manufacturer": "Omron"})
s.R("10k", "LED_N", "+3V3")
s.R("1k", "+3V3", "LED_A")
s.LED("BLUE", "LED_A", "LED_N")
s.TP("USB_DP", P.TP10, "D+")
s.TP("USB_DM", P.TP10, "D-")
# WiFi antenna (used for ELRS WiFi updates only)
s.C("DNP", "WIFI_RF", fp=P.C0402, dnp=True)
s.L("0R / tune", "WIFI_RF", "WIFI_ANT", fp=P.L0402)
s.C("DNP", "WIFI_ANT", fp=P.C0402, dnp=True)
s.add("eAntenna:Antenna_Chip", "2450AT18A100", pins={"1": "WIFI_ANT"}, fields={"MPN": "2450AT18A100E", "Manufacturer": "Johanson"})

# ============================================================================ RADIO
s = B.sheet("Radio", "radio.kicad_sch")
s.note("SX1281: DC-DC mode (15uH on DCC_SW), 52 MHz crystal (internal load caps), VR_PA feeds RFIO through a choke.\n"
       "RF chain: RFIO -> DC block -> 3rd-order low-pass (1pF / 4.7nH / 1pF, fc ~3.3 GHz) -> u.FL.  START VALUES - tune.")
s.FB("120R@100MHz", "+3V3", "+3V3_RF", fp=P.FB0402, fields={"MPN": "BLM15PX121SN1D"})
s.C("10uF 10V", "+3V3_RF", fp=P.C0603)
s.add("eRFModule:SX1281IMLTRT", pins={
    "VBAT": "+3V3_RF", "VBAT_IO": "+3V3_RF", "VDD_IN": "VREG", "DCC_FB": "VREG", "DCC_SW": "DCC_SW", "VR_PA": "VR_PA",
    "XTA": "XTA", "XTB": "XTB", "GND": "GND", "EP": "GND", "RFIO": "RFIO",
    "~{NSS}": "RADIO_NSS", "SCK": "RADIO_SCK", "MOSI": "RADIO_MOSI", "MISO": "RADIO_MISO",
    "~{NRESET}": "RADIO_RST", "BUSY": "RADIO_BUSY", "DIO1": "RADIO_DIO1", "DIO2": "NC", "DIO3": "NC"})
s.C("100nF", "+3V3_RF")
s.C("100nF", "+3V3_RF")
s.L("15uH", "DCC_SW", "VREG", fp=P.L0805, fields={"MPN": "LQM21PN150MC0", "Manufacturer": "Murata"})
s.C("470nF", "VREG")
s.C("47pF NP0", "VR_PA")
s.C("470nF", "VR_PA")
s.L("47nH (tune)", "VR_PA", "RFIO", fp=P.L0402, fields={"MPN": "LQW15AN47NJ00", "Manufacturer": "Murata"})
s.add("eCrystal:Crystal_GND24", "52MHz 8pF", P.XTAL2016, {"1": "XTA", "3": "XTB", "2": "GND", "4": "GND"},
      fields={"MPN": "X201652MOB4SI", "Manufacturer": "Yangxing", "Note": "SX1280 reference: 52 MHz, +/-10ppm"})
s.R("10k", "RADIO_NSS", "+3V3_RF")
s.C("10pF NP0", "RFIO", "RF1", fp=P.C0402)
s.C("1pF NP0", "RF1", fp=P.C0402)
s.L("4.7nH", "RF1", "RF2", fp=P.L0402, fields={"MPN": "LQP15MN4N7B02", "Manufacturer": "Murata"})
s.C("1pF NP0", "RF2", fp=P.C0402)
s.add("eConnector:Conn_Coaxial", "U.FL", P.UFL, {"1": "RF2", "2": "GND"}, fields={"MPN": "U.FL-R-SMT-1(10)", "Manufacturer": "Hirose"})

NETCLASSES = ([project.netclass("Default", 0.15), project.netclass("RF_50R", 0.3, clearance=0.2)],
              [("/Radio/RF?", "RF_50R"), ("/Radio/RFIO", "RF_50R"), ("/MCU/WIFI_*", "RF_50R")])

HARDWARE_JSON = {
    "serial_rx": 20, "serial_tx": 21,
    "radio_busy": 3, "radio_dio1": 1, "radio_miso": 5, "radio_mosi": 4, "radio_nss": 7, "radio_rst": 2, "radio_sck": 6,
    "power_min": 0, "power_high": 0, "power_max": 0, "power_default": 0, "power_control": 0, "power_values": [13],
    "power_lna_gain": 0,
    "led_red": 8, "led_red_invert": True,
    "button": 9,
}
_d = os.path.join(project.KICAD_DIR, "RXV00")
os.makedirs(_d, exist_ok=True)
json.dump(HARDWARE_JSON, open(os.path.join(_d, "RXV00_hardware.json"), "w"), indent=4)
